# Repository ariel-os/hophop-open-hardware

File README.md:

hophop: Open Hardware
=====================

This repository will contains the design files
for hardware developed for hophop.

Items
-----

* [Grasshopper Nymph](./grasshopper-nymph/README.md)

  Status: Boards built and are being tested.

Branding
--------

These boards are developed as part of the Ariel OS project (as is the hophop stack),
will run Ariel OS based software from the start,
and may come with the Ariel OS logo.

License
-------

Data in this repository is licensed under the terms of [CERN-OHL-P-2.0](https://ohwr.org/cern_ohl_p_v2.pdf),
unless specified differently (when derived from third party content).

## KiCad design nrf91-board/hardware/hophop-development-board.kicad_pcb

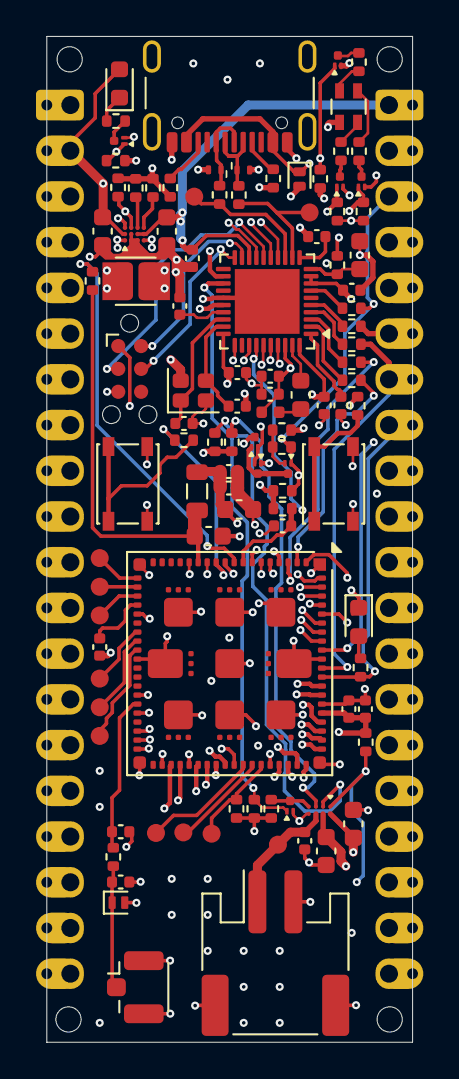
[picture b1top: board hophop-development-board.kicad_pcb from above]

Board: 6 copper layers, 20.3 x 55.9 mm, 107 parts (0 on the bottom side), 107 nets.

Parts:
C201, C405: 4.7uF/16V; C_0603_1608Metric
C202, C204, C503, C504: 10uF/10V; C_0603_1608Metric
C203, C403, C406, C501, C502: 1uF/10V; C_0402_1005Metric
C205: 22uF/6.3V; C_0603_1608Metric
C401, C402, C410, C507, C508: 100nF/16V; C_0402_1005Metric
C404, C408, C505, C506: 4.7uF/10V; C_0402_1005Metric
C407: 47nF/16V; C_0402_1005Metric
C409: 100pF/50V; C_0402_1005Metric
C411, C412: 12pF/50V; C_0402_1005Metric
C509, C510: DNP; C_0402_1005Metric
D201: PESD5V0S1ULSYL; D_SOD-882D
D202, D203: TPD1E05U06DPYR; Texas_DPY0002A_0.6x1mm_P0.65mm
D301: APTF1616LSEEZGKQBKC; LED_Kingbright_APTF1616LSEEZGKQBKC
D302: 150060VS75000; LED_0603_1608Metric
D501: APTD1608LSYCK; LED_0603_1608Metric
D502: DNP; D_SOD-882
J201: USB_C_Receptacle_USB2.0_16P; USB_C_Receptacle_GCT_USB4105-xx-A_16P_TopMnt_Horizontal_NPT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
J202: JST PH S2B-PH-SM4-TB; JST_PH_S2B-PH-SM4-TB_1x02-1MP_P2.00mm_Horizontal
J401: Conn_ARM_SWD_TagConnect_TC2030-NL; Tag-Connect_TC2030-IDC-NL_2x03_P1.27mm_Vertical
J501: U.FL; U.FL_Hirose_U.FL-R-SMT-1_Vertical
J601: Castellated_1x20; CastellatedHeader_1x20_P2.54mm_Drill1.0mm_Left
J602: Castellated_1x20; CastellatedHeader_1x20_P2.54mm_Drill1.0mm_Right
L201: 2.2uH; L_Cenker_CKCS201610
L401: 10uH; L_0603_1608Metric
L402: 15nH; L_0402_1005Metric
L501: 22R@100M/6A; L_0805_2012Metric
Q201, Q301, Q302, Q303, Q304, Q502, Q503: DMN2990UFA; Diodes_X2-DFN0806-3_0.8x0.6mm_P0.35mm_GSD
Q501: DMP22D4UFA; Diodes_X2-DFN0806-3_0.8x0.6mm_P0.35mm_GSD
R201, R202: 5.1K; R_0402_1005Metric
R203, R205, R401, R402, R403, R405, R406: 33R; R_0402_1005Metric
R204, R206, R207, R208, R501, R502: 10K; R_0402_1005Metric
R209, R210, R301, R304, R307, R310, R506: 1M; R_0402_1005Metric
R211: 16.2K; R_0402_1005Metric
R212, R508: 0R; R_0402_1005Metric
R302, R303, R305, R309: 2K; R_0402_1005Metric
R306, R308, R505: 1K; R_0402_1005Metric
R404: 2.2R; R_0402_1005Metric
R503: 100K; R_0402_1005Metric
R504: DNP; R_0402_1005Metric
R507: 4.7K; R_0402_1005Metric
SW301, SW302: PTS810SJM250SMTR LFS; SW_SPST_PTS810
TP201, TP202, TP203, TP501, TP502, TP503, TP504, TP505, TP506, TP507, TP508, TP509: TestPoint; TestPoint_Pad_D1.0mm_Compact
U201: BQ25180YBG; Texas_YBG0008-C01_DSBGA-8_1.04x1.59mm_Layout2x4_P0.4mm
U202: TPS63901YCJ; Texas_YCJ0012-C02_DSBGA-12_1.15x1.5mm_Layout3x4_P0.35mm
U401: nRF52820-QDAA; QFN-40-1EP_5x5mm_P0.4mm_EP3.6x3.6mm
U501: nRF9151-LACA; Nordic_nRF9151-LAxx_LGA-80-33EP_12.1x11.1mm_P0.5mm
Y401: 32MHz; Crystal_SMD_2016-4Pin_2.0x1.6mm

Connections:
+BATT: C203.1, J202.1, TP202.1 (1_1), U201.C2 (BAT)
/LED Sheet/IF_LED_BLUE: Q303.G, R307.2, U401.14 (P0.14)
/LED Sheet/IF_LED_GREEN: Q302.G, R304.2, U401.15 (P0.15)
/LED Sheet/IF_LED_PWR: Q304.G, R310.2, U401.22 (P0.16)
/LED Sheet/IF_LED_RED: Q301.G, R301.2, U401.17 (P0.20)
/LED Sheet/IF_MODE_DFU: R308.2, U401.33 (P0.30)
/LED Sheet/LED_B: Q303.D, R305.2
/LED Sheet/LED_G: Q302.D, R303.2
/LED Sheet/LED_R: Q301.D, R302.2
/LED Sheet/NRF91_USR: R306.2, U501.12 (TRACEDATA3/P0.25)
/MCU Interface Sheet/DEC_4_6: C406.2, C407.2, L402.2, U401.26 (DEC6), U401.38 (DEC4)
/MCU Interface Sheet/IF_HW_RST: Q201.G, R209.2, U401.23 (P0.17)
/MCU Interface Sheet/IF_I2C_INT: R208.1, U201.A1 (~INT), U401.34 (P0.28)
/MCU Interface Sheet/IF_I2C_SCL: R206.2, U201.B1 (SCL), U401.35 (AIN1/P0.03)
/MCU Interface Sheet/IF_I2C_SDA: R207.2, U201.C1 (SDA), U401.36 (AIN0/P0.02)
/MCU Interface Sheet/IF_USB_D+: R205.2, TP203.1 (1_1), U401.13 (D+)
/MCU Interface Sheet/IF_USB_D-: R203.2, TP201.1 (1_1), U401.12 (D-)
/MCU Interface Sheet/IF_VSEL: R210.2, U202.B3 (SEL), U401.31 (P0.08)
/MCU Interface Sheet/NRF91_RESET: J602.3, Q501.G, Q503.G, R403.2, R503.2, R504.1
/MCU Interface Sheet/NRF91_RXD: J602.6, R406.2, U501.72 (P0.12)
/MCU Interface Sheet/NRF91_SWDCLK: J602.4, R401.2, U501.3 (SWDCLK)
/MCU Interface Sheet/NRF91_SWDIO: J602.5, R402.2, U501.4 (SWDIO)
/MCU Interface Sheet/NRF91_TXD: J602.7, R405.2, U501.70 (P0.11)
/MCU Interface Sheet/P0.00/XL1: R401.1, U401.2 (XL1/P0.00)
/MCU Interface Sheet/P0.01/XL2: R402.1, U401.3 (XL2/P0.01)
/MCU Interface Sheet/P0.04/AIN2: R405.1, U401.4 (AIN2/P0.04)
/MCU Interface Sheet/P0.05/AIN3: R406.1, U401.5 (AIN3/P0.05)
/MCU Interface Sheet/P0.18/~RESET: J401.3 (~RESET), U401.16 (P0.18/~RESET)
/MCU Interface Sheet/RESET: R403.1, U401.7 (P0.07)
/MCU Interface Sheet/SWDCLK: J401.4 (SWCLK), U401.20 (SWDCLK)
/MCU Interface Sheet/SWDIO: J401.2 (SWDIO), U401.19 (SWDIO)
/NRF9151 module Sheet/P0.00: J601.14, U501.56 (P0.00)
/NRF9151 module Sheet/P0.01: J601.13, U501.57 (P0.01)
/NRF9151 module Sheet/P0.02: J601.12, U501.58 (P0.02)
/NRF9151 module Sheet/P0.03: J601.11, U501.59 (P0.03)
/NRF9151 module Sheet/P0.04: J601.10, U501.61 (P0.04)
/NRF9151 module Sheet/P0.05: J601.9, U501.62 (P0.05)
/NRF9151 module Sheet/P0.06: J601.8, U501.63 (P0.06)
/NRF9151 module Sheet/P0.07: J601.7, U501.64 (P0.07)
/NRF9151 module Sheet/P0.08: J601.6, U501.67 (P0.08)
/NRF9151 module Sheet/P0.09: J601.5, U501.68 (P0.09)
/NRF9151 module Sheet/P0.10: J602.8, R507.1, U501.69 (P0.10)
/NRF9151 module Sheet/P0.13/AIN0: J602.20, U501.73 (AIN0/P0.13)
/NRF9151 module Sheet/P0.14/AIN1: J602.19, U501.74 (AIN1/P0.14)
/NRF9151 module Sheet/P0.15/AIN2: J602.18, U501.75 (AIN2/P0.15)
/NRF9151 module Sheet/P0.16/AIN3: J602.17, U501.77 (AIN3/P0.16)
/NRF9151 module Sheet/P0.17/AIN4: J602.16, U501.78 (AIN4/P0.17)
/NRF9151 module Sheet/P0.18/AIN5: J602.15, U501.79 (AIN5/P0.18)
/NRF9151 module Sheet/P0.19/AIN6: J602.14, U501.80 (AIN6/P0.19)
/NRF9151 module Sheet/P0.20/AIN7: J602.13, U501.2 (AIN7/P0.20)
/NRF9151 module Sheet/P0.21: J602.12, U501.5 (TRACECLK/P0.21)
/NRF9151 module Sheet/P0.22: J602.11, U501.6 (TRACEDATA0/P0.22)
/NRF9151 module Sheet/P0.23: J602.10, U501.8 (TRACEDATA1/P0.23)
/NRF9151 module Sheet/P0.24: J602.9, U501.11 (TRACEDATA2/P0.24)
/NRF9151 module Sheet/P0.26: J601.20, U501.44 (P0.26)
/NRF9151 module Sheet/P0.27: J601.19, U501.45 (P0.27)
/NRF9151 module Sheet/P0.28: J601.18, U501.47 (P0.28)
/NRF9151 module Sheet/P0.29: J601.17, U501.48 (P0.29)
/NRF9151 module Sheet/P0.30: J601.16, U501.49 (P0.30)
/NRF9151 module Sheet/P0.31: J601.15, U501.50 (P0.31)
/NRF9151 module Sheet/SYS_EN: J601.4, R501.1, U202.A3 (EN), U501.10 (ENABLE)
/NRF9151 module Sheet/~RESET: Q502.D, R504.2, R505.2
/PSU Sheet/D+: D203.1 (K), J201.A6 (D+), J201.B6 (D+), R205.1
/PSU Sheet/D-: D202.1 (K), J201.A7 (D-), J201.B7 (D-), R203.1
GND: C201.2, C202.2, C203.2, C204.2, C205.2, C401.1, C402.2, C403.1, C404.1, C405.2, C406.1, C407.1, C408.1, C409.1, C410.1, C411.2, C412.2, C501.1, C502.1, C503.1, C504.1, C505.1, C506.1, C507.1, C508.1, C509.1, C510.1, D201.2 (A), D202.2 (A), D203.2 (A), D501.1 (K), D502.2 (A2), J201.A1 (GND), J201.A12 (GND), J201.B1 (GND), J201.B12 (GND), J201.SH (SHIELD), J202.2, J202.MP (MountPin), J401.5 (GND), J501.2 (Ext), J601.3, J602.2, Q201.S, Q301.S, Q302.S, Q303.S, Q304.S, Q502.S, Q503.S, R201.2, R202.2, R204.2, R209.1, R210.1, R211.1, R212.1, R301.1, R304.1, R307.1, R310.1, R506.1, SW301.2, SW302.2, U201.D2 (GND), U202.B1 (GND), U202.B2 (CFG1), U202.C1 (GND), U401.25 (VSS_PA), U401.37 (VSS), U401.41 (VSS), U501.1 (GND), U501.7 (GND), U501.13 (GND), U501.15 (GND), U501.20 (GND), U501.25 (GND), U501.30 (GND), U501.34 (GND), U501.36 (GND), U501.38 (GND), U501.39 (GND), U501.40 (GND), U501.41 (GND), U501.43 (GND), U501.46 (GND), U501.51 (GND), U501.55 (GND), U501.60 (GND), U501.66 (GND), U501.71 (GND), U501.76 (GND), U501.105 (GND), U501.106 (GND), U501.107 (GND), U501.108 (GND), U501.109 (GND), U501.110 (GND), U501.111 (GND), U501.112 (GND), U501.113 (GND), Y401.2 (G), Y401.4 (G)
unnamed: D301.4 (BK), R305.1
unnamed: D301.3 (GK), R303.1
unnamed: D301.2 (RK), R302.1
unnamed: D302.1 (K), R309.2
unnamed: D501.2 (A), R507.2
unnamed: C509.2, D502.1 (A1), J501.1 (In), R508.2
unnamed: J201.A5 (CC1), R201.1
unnamed: J201.B5 (CC2), R202.1
unnamed: L401.2, L402.1
unnamed: Q304.D, R309.1
unnamed: Q501.D, Q502.G, Q503.D
unnamed: Q501.S, R502.1, R503.1
unnamed: R306.1, SW301.1
unnamed: R308.1, SW302.1
unnamed: Q201.D, R204.1, U201.D1 (TS/MR)
unnamed: R212.2, U202.C3 (CFG2)
unnamed: R211.2, U202.D3 (CFG3)
unnamed: L201.2, U202.A1 (LX1)
unnamed: L201.1, U202.D1 (LX2)
unnamed: L401.1, U401.39 (DCC)
unnamed: C410.2, U401.1 (DEC1)
unnamed: C409.2, U401.27 (DEC3)
unnamed: C408.2, U401.11 (DECUSB)
unnamed: C405.1, R404.1, U401.10 (VBUS)
unnamed: C411.1, U401.28 (XC1), Y401.1
unnamed: C412.1, U401.29 (XC2), Y401.3
unnamed: C510.2, R508.1, U501.35 (ANT)
unnamed: TP501.1 (1_1), U501.52 (COEX0)
unnamed: TP502.1 (1_1), U501.53 (COEX1)
unnamed: R506.2, TP503.1 (1_1), U501.54 (COEX2)
unnamed: C505.2, U501.24 (DEC0)
unnamed: TP505.1 (1_1), U501.21 (MAGPIO0)
unnamed: TP507.1 (1_1), U501.22 (MAGPIO1)
unnamed: TP509.1 (1_1), U501.23 (MAGPIO2)
unnamed: TP506.1 (1_1), U501.28 (SCLK)
unnamed: TP508.1 (1_1), U501.27 (SDATA)
unnamed: C504.2, L501.2, R501.2, U501.14 (VDD)
unnamed: TP504.1 (1_1), U501.29 (VIO)
unnamed: C508.2, R505.1, U501.9 (~RESET)
VBUS: C201.1, D201.1 (K), J201.A4 (VBUS), J201.A9 (VBUS), J201.B4 (VBUS), J201.B9 (VBUS), J601.1, R404.2, U201.A2 (IN)
VDD_GPIO: C205.1, C401.2, C402.1, C403.2, C404.2, C506.2, C507.2, J401.1 (VCC), J602.1, R206.1, R207.1, R208.2, R502.2, U202.C2 (VOUT), U202.D2 (VOUT), U401.8 (VDD), U401.9 (VDDH), U401.18 (VDD), U401.30 (VDD), U401.40 (VDD), U501.65 (VDD_GPIO)
VSYS: C202.1, C204.1, C501.2, C502.2, C503.2, D301.1 (A), D302.2 (A), J601.2, L501.1, U201.B2 (SYS), U202.A2 (VIN)

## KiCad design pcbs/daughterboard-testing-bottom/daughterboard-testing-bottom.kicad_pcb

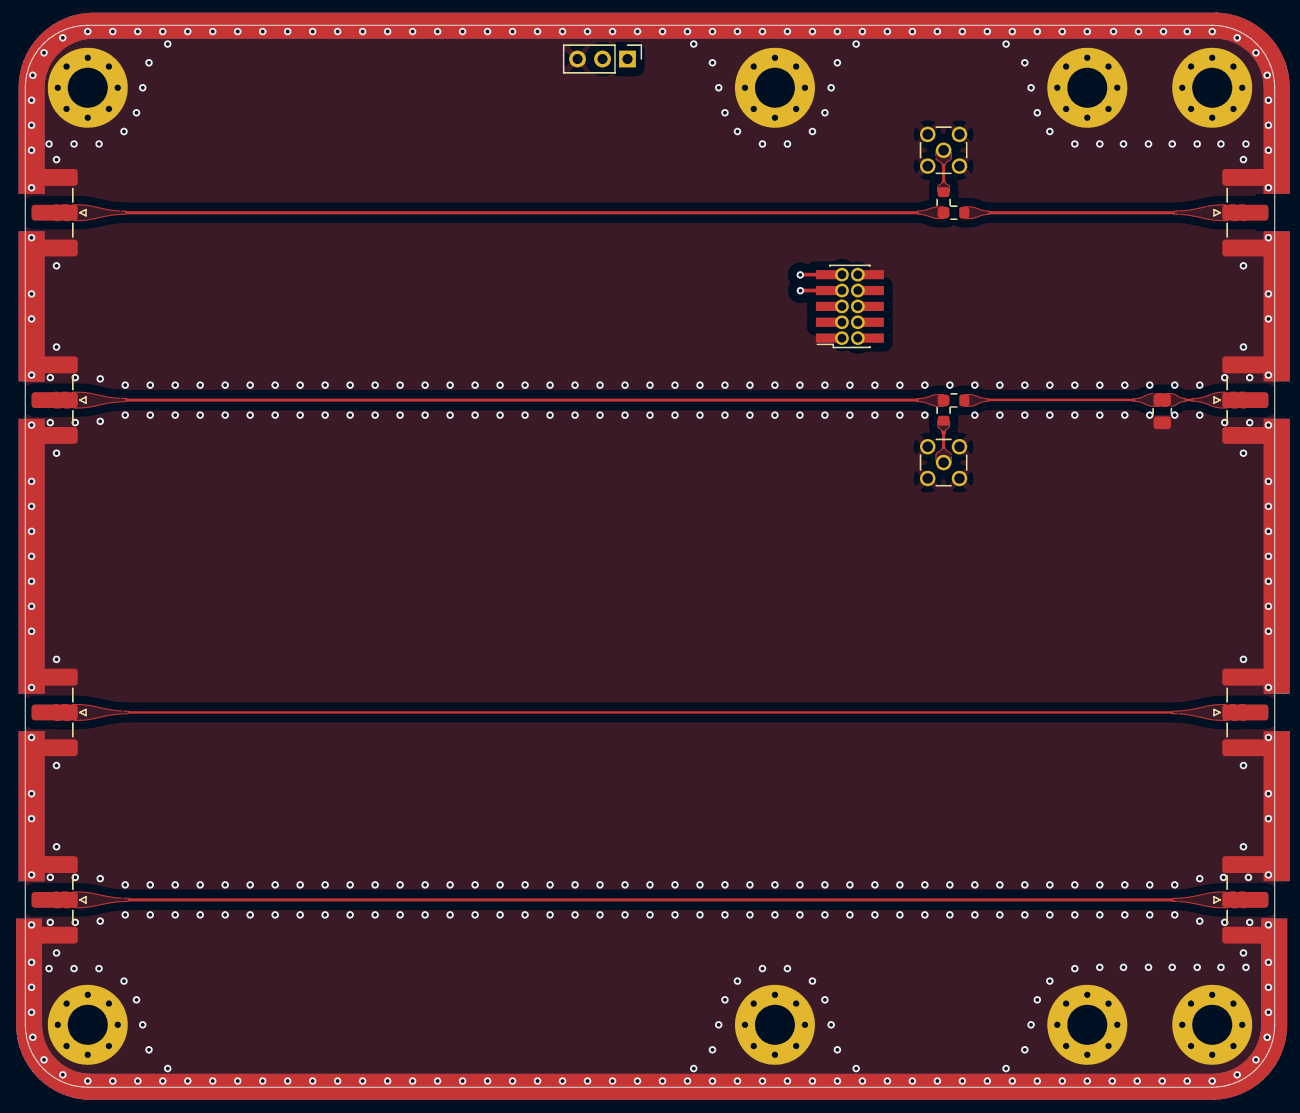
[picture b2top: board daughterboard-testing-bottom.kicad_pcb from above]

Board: 4 copper layers, 100.0 x 85.0 mm, 25 parts (0 on the bottom side), 11 nets.

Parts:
H1, H2, H3, H4, H5, H6, H7, H8: MH_P; MountingHole_3.2mm_M3_Pad_Via
J1, J2: MMCX-J-P-H-ST-TH1; MMCX_Samtec_MMCX-J-P-H-ST-TH1_Vertical
J3, J4, J5, J6, J7, J8, J9, J10: CON-SMA-EDGE-S; SMA_RF_Solutions_CON-SMA-EDGE-S_EdgeMount
J11: 10165448-00010C1LF; PinSocket_2x05_P1.27mm_Vertical_SMD_Holes
J12: 22-27-2031; PinHeader_1x03_P2.00mm_Vertical
R1, R2, R3, R4: 0; R_0603_1608Metric
R5: 50; R_0805_2012Metric

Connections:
/D+: J11.9, J12.1
/D-: J11.7, J12.2
GND: H1.1, H2.1, H3.1, H4.1, H5.1, H6.1, H7.1, H8.1, J1.2 (Ext), J2.2 (Ext), J3.2 (Ext), J4.2 (Ext), J5.2 (Ext), J6.2 (Ext), J7.2 (Ext), J8.2 (Ext), J9.2 (Ext), J10.2 (Ext), J11.1, J11.10, J12.3, R5.2
unnamed: J1.1 (In), R2.1
unnamed: J2.1 (In), R3.1
unnamed: J3.1 (In), R1.1, R2.2
unnamed: J4.1 (In), R3.2, R4.1
unnamed: J5.1 (In), R1.2
unnamed: J6.1 (In), R4.2, R5.1
unnamed: J7.1 (In), J9.1 (In)
unnamed: J8.1 (In), J10.1 (In)

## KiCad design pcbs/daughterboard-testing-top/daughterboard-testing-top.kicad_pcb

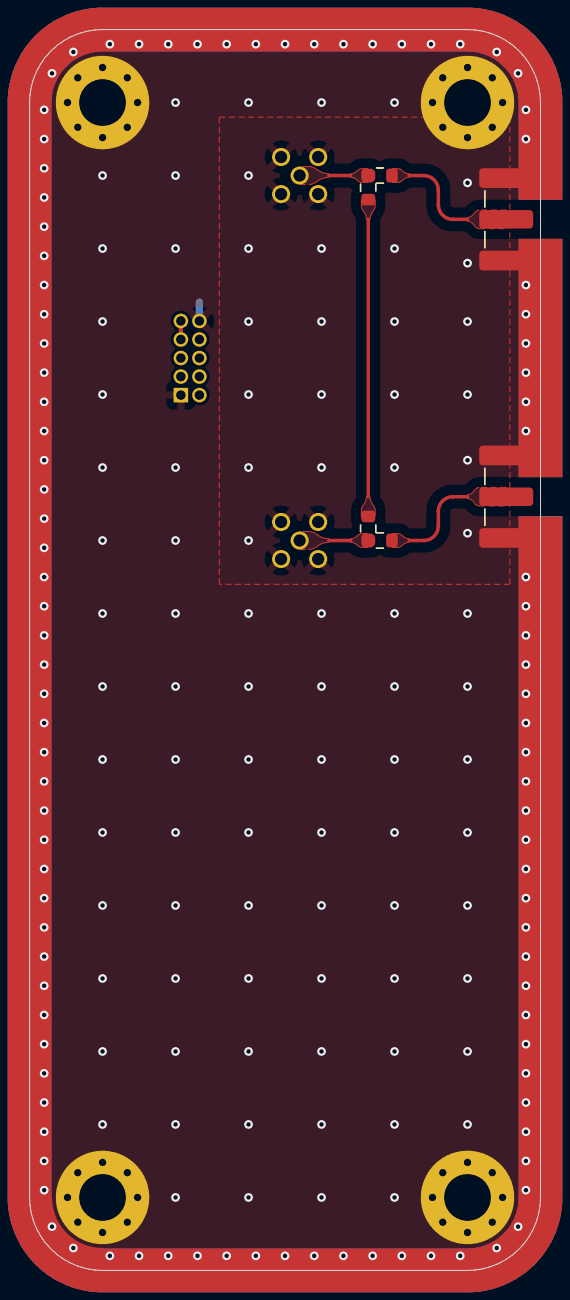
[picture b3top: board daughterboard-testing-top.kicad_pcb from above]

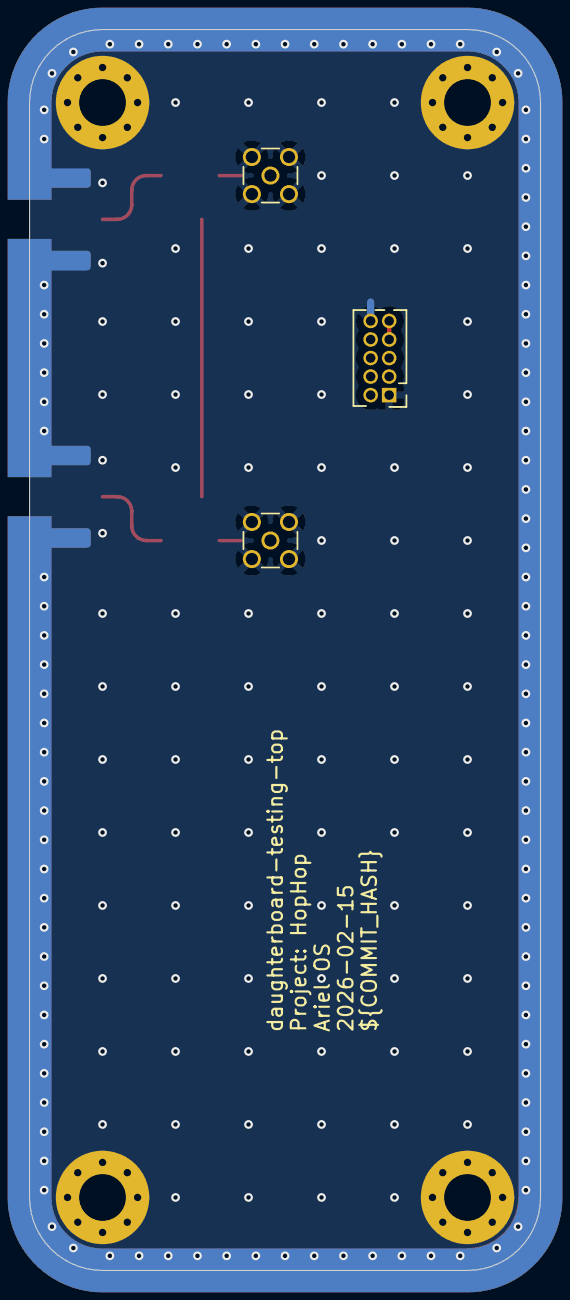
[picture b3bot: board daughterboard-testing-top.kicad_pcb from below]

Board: 4 copper layers, 35.0 x 85.0 mm, 13 parts (3 on the bottom side), 7 nets.

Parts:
H1, H2, H3, H4: MH_P; MountingHole_3.2mm_M3_Pad_Via
J1, J2: CON-SMA-EDGE-S; SMA_RF_Solutions_CON-SMA-EDGE-S_EdgeMount
J3, J4: MMCX-P-P-H-ST-TH1; MMCX_Samtec_MMCX-P-P-H-ST-TH1_Vertical
J5: Conn_02x05_Odd_Even; PinHeader_2x05_P1.27mm_Vertical
R1, R2, R3, R4: 0; R_0603_1608Metric

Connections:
GND: H1.1, H2.1, H3.1, H4.1, J1.2 (Ext), J2.2 (Ext), J3.2 (Ext), J4.2 (Ext), J5.1, J5.10
unnamed: J1.1 (In), R1.2
unnamed: J2.1 (In), R4.1
unnamed: J3.1 (In), R1.1, R2.2
unnamed: J4.1 (In), R3.2, R4.2
unnamed: J5.7, J5.9
unnamed: R2.1, R3.1

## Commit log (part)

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2025-11-13 Original setup
2025-11-13 first sketch
2025-11-14 Clarify 'direct USB control'
2025-11-14 Use consistent Board Control Bus
2025-11-14 Concrete connector and interface suggestions
2025-11-18 Move open questions into issues
    See-Also: https://github.com/ariel-os/hophop-open-hardware/issues/1
    See-Also: https://github.com/ariel-os/hophop-open-hardware/issues/2
2025-11-19 Resolve open PDM question
2025-11-19 Fix typo
2025-11-19 Ariel OS branding
    As per 2025-11-18 weekly
2025-11-19 Organize for better clarity in naming
2025-11-24 Assign license
    Closes: https://github.com/ariel-os/hophop-open-hardware/issues/3
2025-11-25 Setup pcb schematic and board file
2025-11-25 formalize hardware requirements in new file in subfolder
2026-02-16 Add daughterboard testing pcbs (top and bottom)
2026-02-16 replace project name text variable
    ...with hardcoded text, as some manufacturers require upload of
    project-agnostic .kicad_pcb file
2026-02-17 factor out devkit-rev-010
2026-02-17 Move requirements to design-decisions folder for consistency
2026-04-24 add playground
2026-05-01 Add .gitignore
2026-05-01 Rename PowerModule
2026-05-01 WRite HLD
2026-05-01 Remove Readme. Add TechnicalRequirements document
2026-05-01 Add technical requirements and adjust HLD
